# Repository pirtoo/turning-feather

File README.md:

# turning-feather
## Turning controller based on an Adafruit [Feather HUZZAH32](https://www.adafruit.com/product/3405) or [Feather ESP32 V2](https://www.adafruit.com/product/5400)

# This branch

This branch is testing LVGL and associated GUI libraries and a major restructuring of the code.
WiFi connectivity is working, it will create its own WiFI network if it cannot connect elsewhere.
LVGL display with dropdowns for program and stage selections, progress bars for the current exposure/away and for the stage as a whole are working.

Either disable WiFi or set a password on the WiFi network and an admin password on settings change.
There is a config menu on the device to reset settings if they are forgotten, to disable WiFi entirely and a signal strength meter for the ZPT RF remote control.

Still to come are popup messages for any errors or WiFi issues and if the ZPT remote control is low on battery or is not properly paired.

## Features

* More flexible than an [Auto Duel](https://web.archive.org/web/20170504011814/http://www.indelfa.co.uk/tt/ttcontruk.html) controller (and indelfa seem to have vanished), programs defined in JSON in a text file on a micro SD card. Can have a backup config file flashed to SPI accessed via LittleFS.

  * Current maximums of approx 55 programs and up to 12 stages per program (limited by memory in the controller) but will increase with development and it will be easier to swap between sets of programs.

  * [Example config](data/turnconf.txt).

  * Configs can be checked for JSON validity [here](https://arduinojson.org/v7/assistant/) or on any JSON website with a checker.

* Touch screen to select program/stage and start/stop face/away.

* RF remote control via [RF Solutions](https://www.rfsolutions.co.uk/) [ZPT module](https://www.rfsolutions.co.uk/radio-modules/zpt-433-868mhz-radio-telemetry-modules/?searchid=35864&search_query=zpt), compatable with their 4 button [Fobber](https://www.rfsolutions.co.uk/remote-control-systems/fobber-433mhz-868mhz-remote-control-key-fob-transmitter/?searchid=35862&search_query=fobber) or longer range [Trap](https://www.rfsolutions.co.uk/remote-control-systems/trap-handheld-transmitters-868mhz-or-918mhz-versions/?searchid=35863&search_query=trap) remote.

  Remote buttons give:
  * start/stop
  * face/away
  * stage -
  * stage +

  You can set a program and walk down range without needing to return to the unit to run, stop or change stages. The buzzer chirps briefly by default when changing stage from the RF remote so if you are unsure which stage you are in you can go to the first or last stage (when it cannot go further so will not chirp) to establish what stage is set.

  ZPT module can be programmed to respond to several different remotes. See the [ZPT datasheet](https://www.rfsolutions.co.uk/content/download-files/ZPT-3-DATASHEET.pdf) for programming instructions. I keep the learning button internal to the unit so it can't be accidentally activated.

* Display is a [Featherwing 2.4" TFT](https://www.adafruit.com/product/3315) or [Featherwing 2.4" TFT V2](https://www.adafruit.com/product/3315).

* Optional WiFi control, with no configuration and with WiFi enabled the controller will create a WiFi network called `TurningFeather`. Connecting to that network with no password and connecting to `http://192.168.4.1/` will get you to the control page. `http://192.168.4.1/wifisetup.html` will allow you to change setup of network names and joining an existing WiFi network. The MAC address for the controller is displayed on the setup page and also over serial console while booting for setting ststic
IP addresses on your router or IP can be set on the device (not recommended). Pages like `wifisetup.html` can be protected by an admin password (default username is `admin`) but this is all sent over unencrypted HTTP so is not high security, just to keep prying fingers out.

* Control/power connector is RJ45; takes ground, +12V power and two signal lines for face and away activation at 12V. As used [here](https://web.archive.org/web/20190102055407/http://www.indelfa.co.uk/tt/tt_images/relay.gif).  The control and power connections are exposed to another optional board connector if you do not want to use a PCB mounted RJ45.

* [Parts list and assembly details](PCBs/README.md).

## Current state

* Software build and flash [managed by PlatformIO](platformio.md) for different versions of ESP32 and display boards.

* [Custom PCB](PCBs/kicad/turning-feather) made for the main IO board manufactured by [PCBWay](https://www.pcbway.com/project/shareproject/Turning_Feather.html). See [schematic](PCBs/kicad/turning-feather/turning-feather.pdf).

* New generation of graphics are in progress.

* Two physical buttons for face/away and start/stop. Program selection via the touchscreen. Start/stop, face/away and stage +/- via RF remote.

* If `USE_ZPT_SERIAL` is enabled the controller detects when it receives a packet from a remote that is not paired with the comntroller and displays a `?` character in the top right hand corner of the display. Similarly if the battery in the transmitter is low then it will display a `!` character. These characters clear the next time the controller receives a packet from a paired receiver that does not have a low battery.

* With an ESP32 V2 there is a Neopixel LED on the board, if enabled by default this will light up white during initial setup and Red/Green/Blue for beep/face/away during stages. It points backwards but if using the case with a mostly clear front it should be visible to see what part of a stage the unit is in and if it has finished from further away. This can be enabled/disabled with the `ESP_V2_NEOPIXEL` macro and the overall brightness set with `ESP_V2_NEOPIXEL_BRIGHTNESS`

* Spare 5v output for light flash or other features.

## Future plans

Turning Feather is still very much in alpha and under development however it has been in use at one club for over 6 years.

- [ ] Config GUI to change system settings.

- [ ] Signal strength meter for the RFSolutions system.

- [ ] Add a stage name/comment to describe what each stage is for.

- [X] The [Feather HUZZAH32](https://www.adafruit.com/product/3405) microcontroller includes wifi, this will be used for setup, programming and control.

- [ ] Ability to change which config file is in use.

- [X] Updates planned here to provide [parts lists](PCBs/README.md), links, etc, to allow others to build their own units.

- [ ] Provide a full definition of the config file and what all the options do.

- [ ] Add random range options for configs for face/away times.

- [ ] Add the ability to use cheaper 433MHz radio transmitters (there are some nice 4/6 button units available) as an option but getting reliable detection of events with debouncing is hard to do well, unlike with the [RF Solutions](https://www.rfsolutions.co.uk/) units.

- [X] Support for the V2 versions of Adafruit Feather/Featherwing products used.

Other TODOs in the code are noted in the [main ino file](arduino/turning/turning.ino).

No plans to sell pre-made units in any volume but I may have one spare to sell that has not been installed in a case.

## Pull requests invited.

Feature request also invited.

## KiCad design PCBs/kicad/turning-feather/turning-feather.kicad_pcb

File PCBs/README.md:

# turning feather PCB and build

## Parts list to assemble with PCB

| Part | Quantity | Source |
| ---- | -------- | ------ |
| Capacitors |
| 0.1uF | x1 | |
| 22uF | x1 | |
| 470uF | x1 | |
| Resistors |
| 560R | x1 | |
| 2.2kR | x1 | |
| 10kR | x4 | |
| Diodes |
| 3mm LED | x2 | |
| 1N5817 | x4 | https://uk.farnell.com/stmicroelectronics/1n5817/diode-schottky-1a-20v-do-41/dp/9801197 |
| Connectors and cables |
| Socket headers | x1 pack | https://thepihut.com/products/36-pin-swiss-female-socket-headers-pack-of-5 |
| JST-PH 3 way PCB 90 degree | x1 | https://thepihut.com/products/jst-ph-jumper-assembly-3-wire |
| JST-PH 3 way plug and cable | x1 | Included in above |
| JST-PH 4 way PCB 90 degree | x1 | https://thepihut.com/products/jst-ph-jumper-assembly-4-wire |
| JST-PH 4 way plug and cable | x1 | Included in above |
| RJ45 PCB Shielded | x1 | https://uk.farnell.com/wurth-elektronik/615008142621/rj45-conn-r-a-jack-8p8c-1port/dp/2827822?gross_price=true&CMP=KNC-GUK-GEN-SHOPPING-PMAX-HIGH-ROAS&gad_source=1&gad_campaignid=17568744370&gclid=CjwKCAiA09jKBhB9EiwAgB8l-Keu6t1KMnuOvlgZ3LdBT3_u35CNMEyAGO-oGcBRlu94OLG5bAtN4hoCo3kQAvD_BwE |
| Panel Mount Extension USB Cable | x1 | [For Feather V1](https://thepihut.com/products/panel-mount-extension-usb-cable-micro-b-male-to-micro-b-female) [for V2](https://shop.pimoroni.com/products/right-angle-panel-mount-extension-cables-25cm?variant=32013609664595) |
| SMA to uFL cable | x1 | https://thepihut.com/products/sma-to-ufl-u-fl-ipx-ipex-rf-adapter-cable or included with antenna |
| SMA antenna | x1 | https://thepihut.com/products/lora-antenna-with-pigtail-868mhz-black |
| Adafruit Stacking Headers for Feather | x1 | https://thepihut.com/products/stacking-headers-for-feather-12-pin-and-16-pin-female-headers |
| Switches |
| Panel mount DPDT toggle switch | x1 | https://www.adafruit.com/product/3220?srsltid=AfmBOopktvlaYSxf00hTX3HSPP8zWhvR285GFbeFXXPOa2BU2tYauQCs |
| 6mm PCB button | x1 | https://thepihut.com/products/metal-ball-tactile-button-6mm-x-10-pack |
| Panel mount push buttons | x2 | https://thepihut.com/products/12mm-domed-push-button-6-pack |
| Boards and ICs | | |
| Feather ESP32 | x1 | [V1](https://thepihut.com/products/adafruit-huzzah32-esp32-feather-board-pre-soldered-ada3591) [V2](https://thepihut.com/products/adafruit-esp32-feather-v2-w-fl-antenna-8mb-flash-2-mb-psram-stemma-qt) |
| TFT FeatherWing - 2.4" 320x240 | x1 | [V2](https://thepihut.com/products/adafruit-tft-featherwing-2-4-320x240-touchscreen-for-all-feathers) |
| ZPT receiver DIP 868Mhz | x1 | https://www.rfsolutions.co.uk/radio-modules/zpt-433-868mhz-radio-telemetry-modules/?searchid=35864&search_query=zpt |
| TSR 1-2450 | x1 | https://uk.farnell.com/tracopower/tsr-1-2450/converter-dc-dc-5v-1a-sip/dp/1696320 |
| 4427 mosfet driver DIP-8 | x2 | https://uk.farnell.com/maxim-integrated-products/max4427epa/mosfet-driver-high-low-side-dip/dp/2516370 |
| Other |
| PCB | x1 | https://www.pcbway.com/project/shareproject/Turning_Feather.html |
| Remote control 868Mhz 4 buttons | x1 | https://www.rfsolutions.co.uk/remote-control-systems/fobber-433mhz-868mhz-remote-control-key-fob-transmitter/ or https://www.rfsolutions.co.uk/remote-control-systems/trap-handheld-transmitters-868mhz-or-918mhz-versions/ |
| 5v buzzer | x1 | https://thepihut.com/products/buzzer-5v-breadboard-friendly |
| M2.5 plastic standoff kit | x1 | https://thepihut.com/products/adafruit-black-nylon-screw-and-stand-off-set-m2-5-thread |
| Case Grey ABS Box Clear Lid 150x80x76 | x1 | https://thepihut.com/products/small-plastic-project-enclosure-weatherproof-with-clear-top |
| LiPo backup battery | x1 | https://thepihut.com/products/150mah-3-7v-lipo-battery |
| MicroSD card 1Gb-32Gb | x1 | |

One of the 1N5817 diodes should be inserted into the 5v supply line in the panel mount extension cable so when the unit has 12v supply, converting to 5V via the TSR 1-2450, this does not feed back to a USB connected device. 5v can be supplied either through the converter or from USB. If you do not install this diode I would not recommend connecting the controller to 12V and USB at the same time.

Input voltage is stated at 12v since this is what the original system uses. Minimum input voltage via the RJ45 is 6.5v and maxium input voltage is 36v to the TSR 1-2450. Maximum input voltage to the MAX4427EPA+ is 18v. Voltage output to the turn/away signals will be the input voltage.

The DPDT toggle switch turns the unit on and off and connects to J1 via the JST-PH 4 way cable. Pins 2 and 3 to each common on the switch, pin 1 to pin 2 in one position and pin 3 to pin 4 in the other position. In the off position 12v from the PCB RJ45 is not supplied back to the board and the enable pin of the Feather is grounded.

The two panel switches and the buzzer connect to J3 via the JST-PH 3 way cable. Pin 1 to the buzzer positive pin, pin 3 to the buzzer ground. Pin 2 to the first button and to a resistor to the second button and ground to the other button pins. This way when the button is pressed pin 2 is grounded directly, when the other button is pressed pin 2 is grounded via the resistor.

With the HUZZAH32/ESP32 you cannot read analog inputs on ADC #2 once WiFi has started as it is shared with the WiFi module. This pin is used as a digital input from the radio receiver so this should not cause problems. Maximum current output from each output pin is 1.1 mA, hence running the buzzer through a mosfet driver.

## Options

The LiPo battery to connect to the Feather is optional, a small battery is useful for using the controller when not connected to the target system and in case power is temporarily interrupted. A small battery will fit under the Feather board and connect to it.

Instead of using a PCB mounted RJ45 connector the optional J2 connector can be used to connect to 12v supply, ground, and turn/away signals. If you are not using J2 there is no need to fit a connector.

If you do not need a buzzer then U3 can be left off. The output will still flash the onboard LED by default. J3 pin 2 can be left unconnected.

# Assembly

Be careful to orient diodes, LEDs and tantalum/electrolytic capacitors correctly.

Note that some components (RJ45, LEDs and learn button) are placed on the rear side of the PCB.

The ZPT antenna is connected via the uFL connector on the ZPT board.

Plastic M2.5 standoffs should be used to mount the Featherwing display and HUZZAH32 to the IO board. Note that two of the mounting holes on the HUZZAH32 are partially obscured by the onboard 2.4GHz antenna so cannot be used.

V2 of the Adafruit ESP32 Feather is now supported as are V2 Adafruit display Featherwings, make sure to build the correct version for the hardware revisions you have. An ESP32 is required for the current code since it uses ESP32 timers.

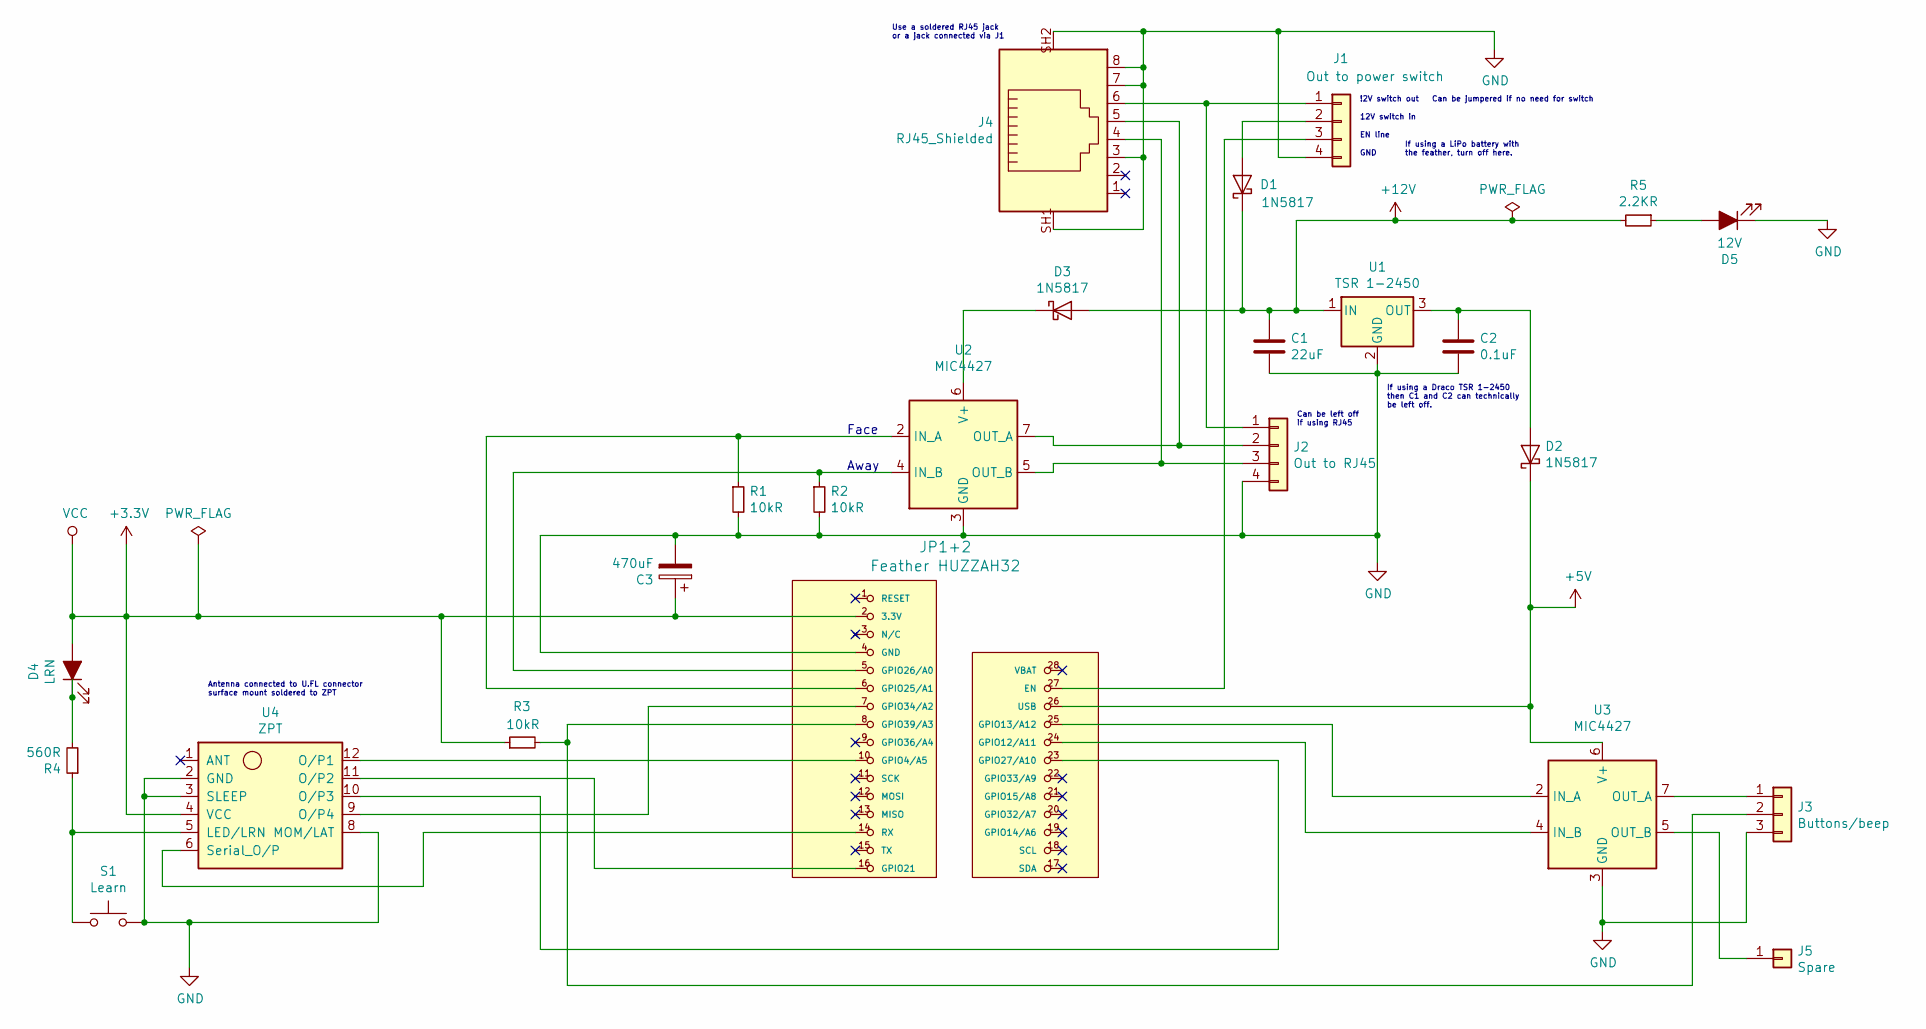
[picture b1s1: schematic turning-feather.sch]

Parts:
C1: 22uF; CP_Radial_Tantal_D4.5mm_P2.50mm
C2: 0.1uF; C_Disc_D3.0mm_W2.0mm_P2.50mm
C3: 470uF; CP_Radial_D6.3mm_P2.50mm
D1, D2, D3: 1N5817; D_DO-41_SOD81_P10.16mm_Horizontal
D4: LRN; LED_D3.0mm_Clear
D5: 12V; LED_D3.0mm_Clear
J1: Out to power switch; JST_PH_S4B-PH-K_1x04_P2.00mm_Horizontal
J2: Out to RJ45; JST_PH_S4B-PH-K_1x04_P2.00mm_Horizontal
J3: Buttons/beep; JST_PH_S3B-PH-K_1x03_P2.00mm_Horizontal
J4: RJ45_Shielded; RJ45_Horizontal_Shielded
J5: Spare; PinHeader_1x01_P1.00mm_Vertical
JP1+2: Feather HUZZAH32; ADAFRUIT_FEATHER
R1, R2, R3: 10kR; R_Axial_DIN0207_L6.3mm_D2.5mm_P7.62mm_Horizontal
R4: 560R; R_Axial_DIN0207_L6.3mm_D2.5mm_P7.62mm_Horizontal
R5: 2.2KR; R_Axial_DIN0207_L6.3mm_D2.5mm_P7.62mm_Horizontal
S1: Learn; SW_PUSH_6mm_H5mm
U1: TSR 1-2450; Converter_DCDC_TRACO_TSR-1_THT
U2, U3: MIC4427; DIP-8_W7.62mm
U4: ZPT; ZPT8RD

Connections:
+3V3: C3.1, D4.2 (A), JP1+2.2 (3.3V), R3.1, U4.4 (VCC)
+5V: D2.1 (K), JP1+2.26 (USB), U3.6 (V+)
+12V: C1.1, D1.1 (K), D3.2 (A), R5.2, U1.1 (IN)
GND: C1.2, C2.2, C3.2, D5.1 (K), J1.4, J2.4, J3.3, J4.3, J4.7, J4.8, J4.SH1, J4.SH2, JP1+2.4 (GND), R1.2, R2.2, S1.2, U1.2 (GND), U2.3 (GND), U3.3 (GND), U4.2 (GND), U4.3 (SLEEP), U4.8 (MOM/LAT)
unnamed: C2.1, D2.2 (A), U1.3 (OUT)
unnamed: D1.2 (A), J1.2
unnamed: D3.1 (K), U2.6 (V+)
unnamed: D4.1 (K), R4.2
unnamed: D5.2 (A), R5.1
unnamed: J1.1, J2.1, J4.6
unnamed: J1.3, JP1+2.27 (EN)
unnamed: J2.2, J4.5, U2.7 (OUT_A)
unnamed: J2.3, J4.4, U2.5 (OUT_B)
unnamed: J3.1, U3.7 (OUT_A)
unnamed: J3.2, JP1+2.8 (GPIO39/A3), R3.2
unnamed: J5.1, U3.5 (OUT_B)
unnamed: JP1+2.5 (GPIO26/A0), R2.1, U2.4 (IN_B)
unnamed: JP1+2.6 (GPIO25/A1), R1.1, U2.2 (IN_A)
unnamed: JP1+2.7 (GPIO34/A2), U4.9 (O/P4)
unnamed: JP1+2.10 (GPIO4/A5), U4.12 (O/P1)
unnamed: JP1+2.14 (RX), U4.6 (Serial_O/P)
unnamed: JP1+2.16 (GPIO21), U4.11 (O/P2)
unnamed: JP1+2.23 (GPIO27/A10), U4.10 (O/P3)
unnamed: JP1+2.24 (GPIO12/A11), U3.4 (IN_B)
unnamed: JP1+2.25 (GPIO13/A12), U3.2 (IN_A)
unnamed: R4.1, S1.1, U4.5 (LED/LRN)

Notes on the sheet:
Face
Away
If using a Draco TSR 1-2450 then C1 and C2 can technically be left off.
If using a LiPo battery with the feather, turn off here.
Antenna connected to U.FL connector surface mount soldered to ZPT
Use a soldered RJ45 jack or a jack connected via J1
Can be jumpered if no need for switch
Can be left off if using RJ45
!2V switch out
12V switch in
EN line
GND

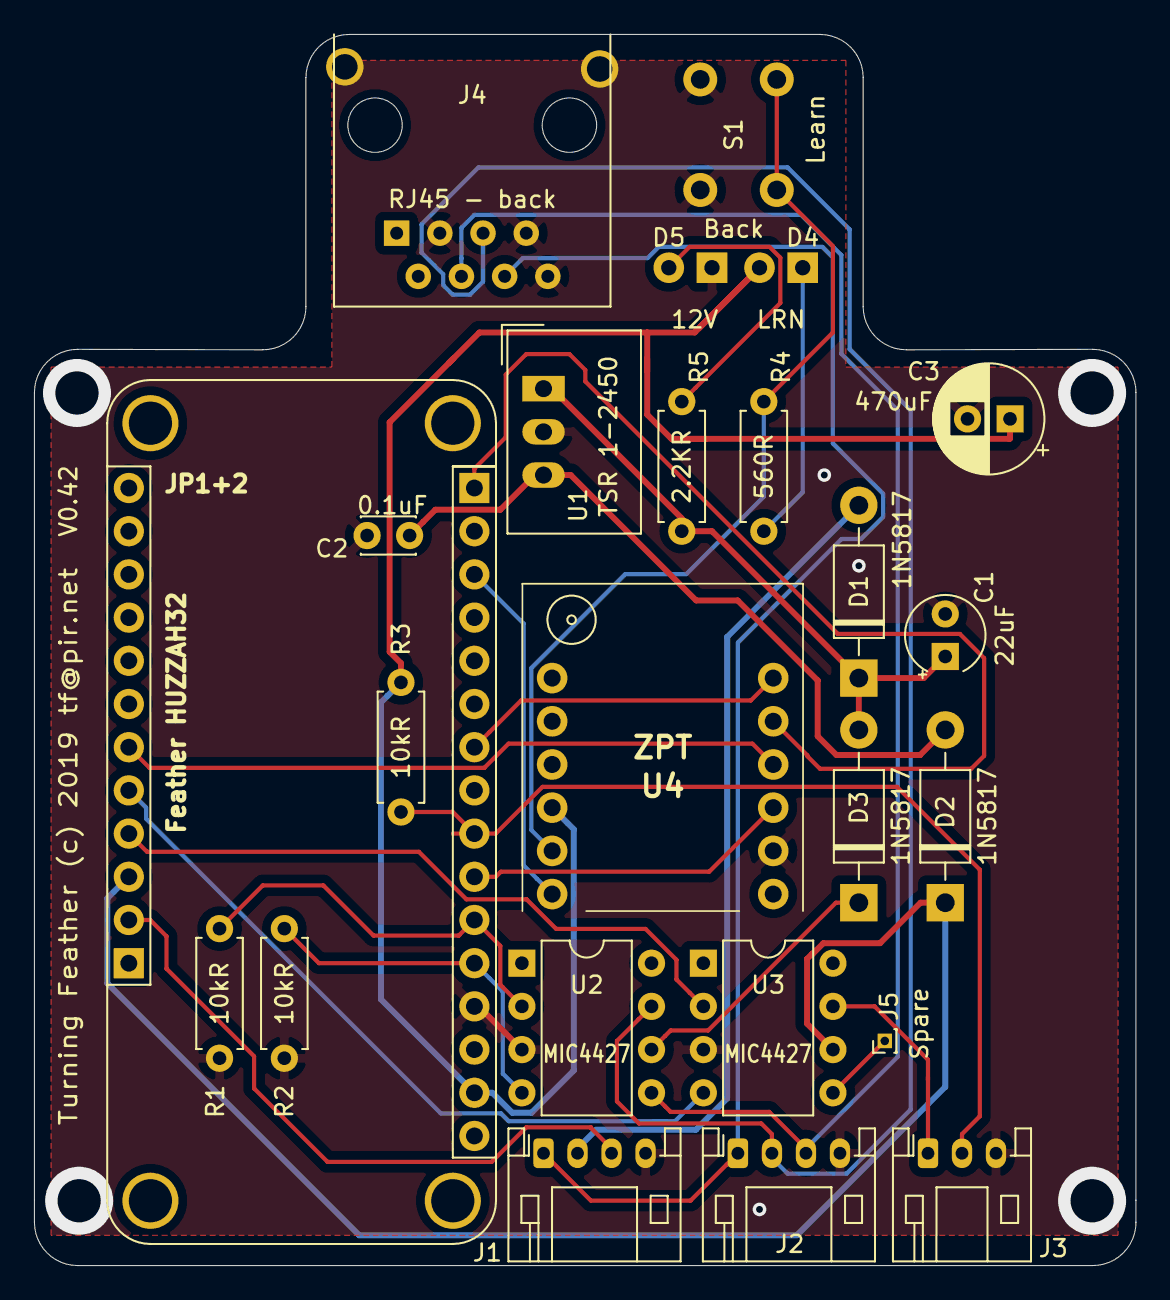
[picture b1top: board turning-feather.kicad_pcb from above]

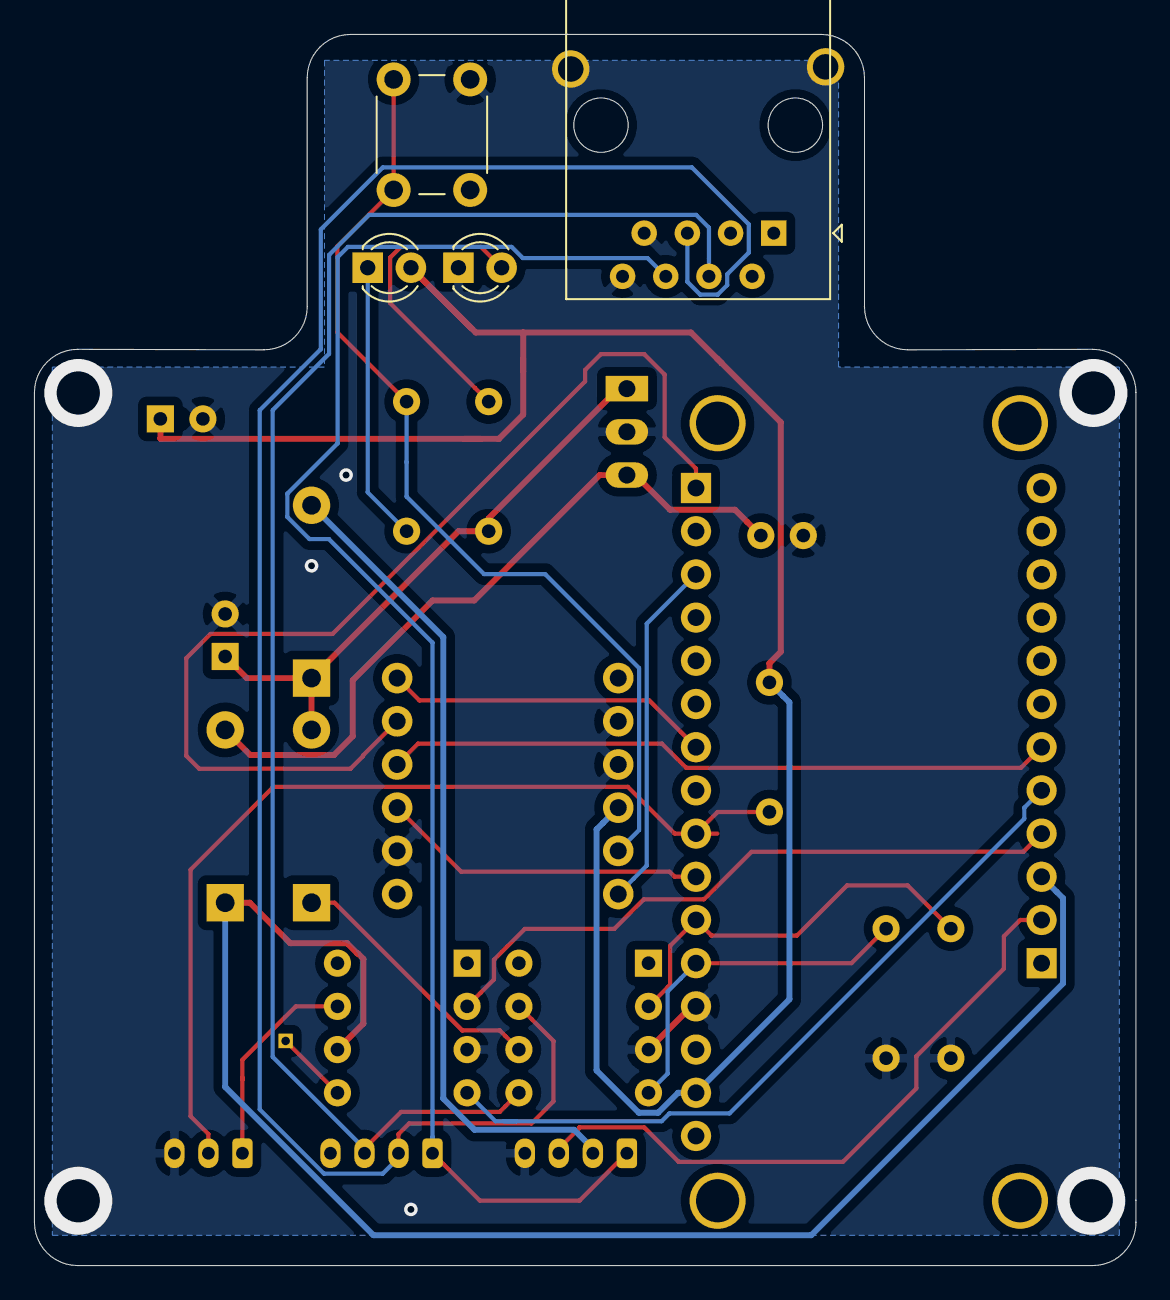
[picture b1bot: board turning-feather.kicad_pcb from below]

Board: 2 copper layers, 64.8 x 72.4 mm, 24 parts (4 on the bottom side), 26 nets.

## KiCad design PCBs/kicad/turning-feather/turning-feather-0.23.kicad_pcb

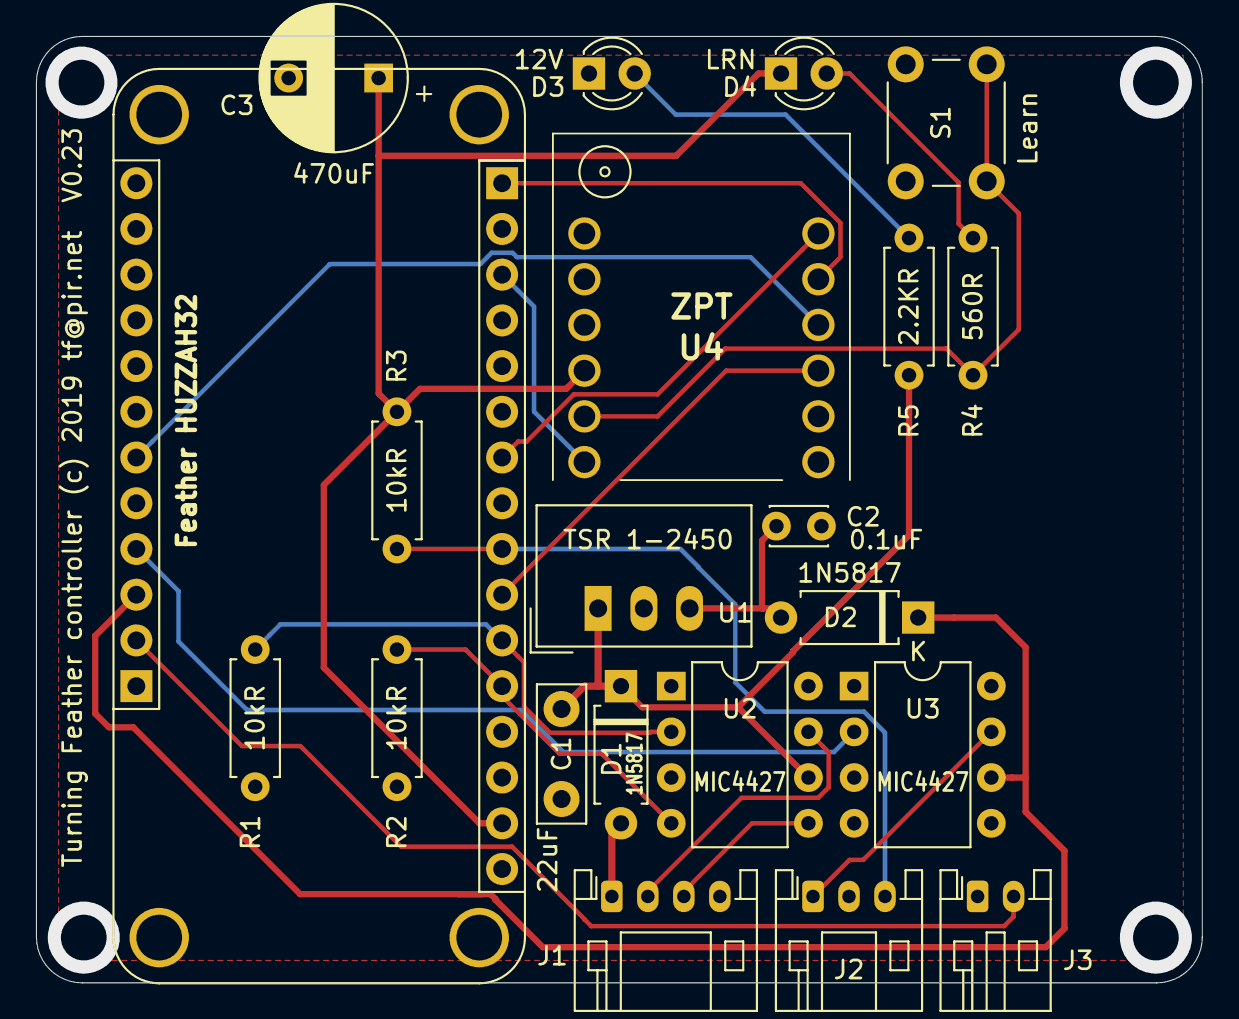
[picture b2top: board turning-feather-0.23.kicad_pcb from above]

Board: 2 copper layers, 64.8 x 52.6 mm, 21 parts (0 on the bottom side), 22 nets.

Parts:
C1: 22uF; C_Disc_D7.5mm_W2.5mm_P5.00mm
C2: 0.1uF; C_Disc_D3.0mm_W2.0mm_P2.50mm
C3: 470uF; CP_Radial_D8.0mm_P5.00mm
D1, D2: 1N5817; D_A-405_P7.62mm_Horizontal
D3: 12V; LED_D3.0mm_Clear
D4: LRN; LED_D3.0mm_Clear
J1: Out to RJ45; JST_PH_S4B-PH-K_1x04_P2.00mm_Horizontal
J2: Buttons/beep; JST_PH_S3B-PH-K_1x03_P2.00mm_Horizontal
J3: Off switch; JST_PH_S2B-PH-K_1x02_P2.00mm_Horizontal
JP1: Feather HUZZAH32; ADAFRUIT_FEATHER
R1, R2, R3: 10kR; R_Axial_DIN0207_L6.3mm_D2.5mm_P7.62mm_Horizontal
R4: 560R; R_Axial_DIN0207_L6.3mm_D2.5mm_P7.62mm_Horizontal
R5: 2.2KR; R_Axial_DIN0207_L6.3mm_D2.5mm_P7.62mm_Horizontal
S1: Learn; SW_PUSH_6mm_H5mm
U1: TSR 1-2450; Converter_DCDC_TRACO_TSR-1_THT
U2, U3: MIC4427; DIP-8_W7.62mm
U4: ZPT; ZPT8RD

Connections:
+3V3: C3.1, D4.1, JP1.2, R3.1, U4.4
+5V: D2.1, JP1.26, U3.6
+12V: C1.1, D1.1, R5.1, U1.1, U2.6
GND: C1.2, C2.2, C3.2, D3.1, J1.4, J2.2, J3.1, JP1.4, R1.2, R2.2, S1.2, U1.2, U2.3, U3.3, U4.2, U4.3, U4.8
unnamed: C2.1, D2.2, U1.3
unnamed: D1.2, J1.1
unnamed: D3.2, R5.2
unnamed: D4.2, R4.2
unnamed: J1.2, U2.7
unnamed: J1.3, U2.5
unnamed: J2.1, U3.7
unnamed: J2.3, JP1.8, R3.2
unnamed: J3.2, JP1.27
unnamed: JP1.5, R2.1, U2.4
unnamed: JP1.6, R1.1, U2.2
unnamed: JP1.7, U4.9
unnamed: JP1.10, U4.12
unnamed: JP1.14, U4.6
unnamed: JP1.16, U4.11
unnamed: JP1.23, U4.10
unnamed: JP1.25, U3.2
unnamed: R4.1, S1.1, U4.5

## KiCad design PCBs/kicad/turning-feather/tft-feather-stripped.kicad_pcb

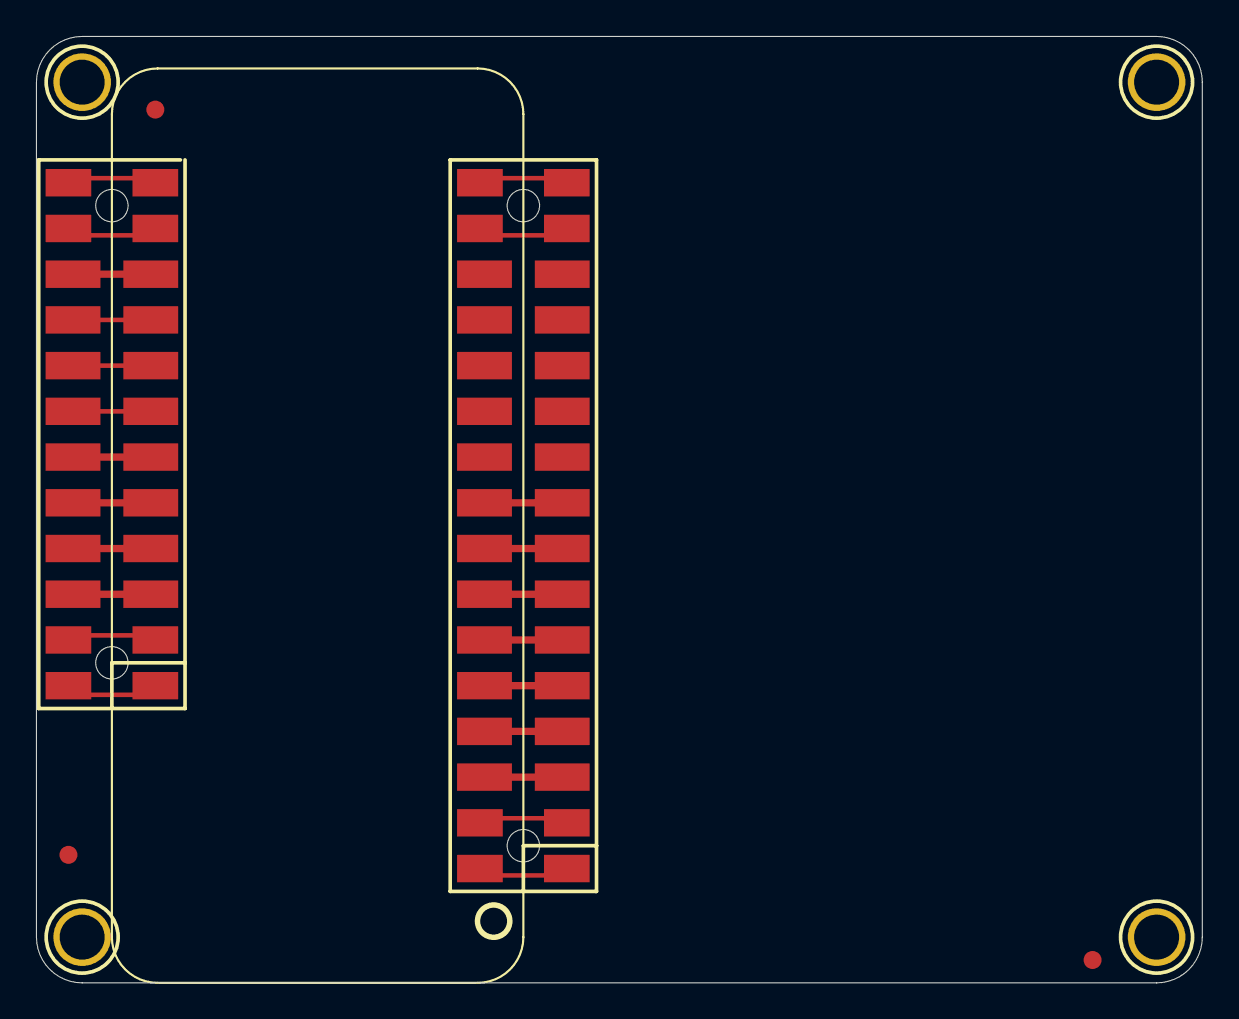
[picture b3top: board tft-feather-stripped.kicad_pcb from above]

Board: 16 copper layers, 64.8 x 52.6 mm, 9 parts (0 on the bottom side), 28 nets.

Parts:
FID1, FID2, FID3: FIDUCIAL; FIDUCIAL_1MM
MS2: FEATHERWING_SMTDUAL; FEATHERWING_SMT2
U$9, U$11, U$15, U$17: MOUNTINGHOLE2.5; MOUNTINGHOLE_2.5_PLATED
U$34: PCBFEAT-REV-040

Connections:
3.3V: MS2.2, MS2.2'
/MISO: MS2.13, MS2.13'
/MOSI: MS2.12, MS2.12'
/SCLK: MS2.11, MS2.11'
GND: MS2.4, MS2.4'
unnamed: MS2.1, MS2.1'
unnamed: MS2.3, MS2.3'
unnamed: MS2.5, MS2.5'
unnamed: MS2.6, MS2.6'
unnamed: MS2.7, MS2.7'
unnamed: MS2.8, MS2.8'
unnamed: MS2.9, MS2.9'
unnamed: MS2.10, MS2.10'
unnamed: MS2.14, MS2.14'
unnamed: MS2.15, MS2.15'
unnamed: MS2.16, MS2.16'
unnamed: MS2.17, MS2.17'
unnamed: MS2.18, MS2.18'
unnamed: MS2.19, MS2.19'
unnamed: MS2.20, MS2.20'
unnamed: MS2.21, MS2.21'
unnamed: MS2.22, MS2.22'
unnamed: MS2.23, MS2.23'
unnamed: MS2.24, MS2.24'
unnamed: MS2.25, MS2.25'
unnamed: MS2.26, MS2.26'
unnamed: MS2.27, MS2.27'
unnamed: MS2.28, MS2.28'

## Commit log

2019-08-28 Initial set of arduino files and kicad files for turning feather
2019-08-28 Add to readme a little
2019-08-29 Set to max programs tested and clean up some error output
2019-08-29 Reformat a print and add a TODO
2019-08-29 Add serial output from ZPT to serial in on feather. PCB V0.23.
2019-08-29 Update schematic with plotted pdf
2019-08-31 Add parsing of ZPT serial data and unify block comment styles
    The ZPT unit outputs a serial data packet format with information
    about received signal from a transmitter. If this is connected to Serial2
    on the feather HUZZAH32 we can parse it and get informaiton such as
    transmitter low battery or if the button has been learned by the
    receiver and print up a status character int the top right to warn the user
    '!' means low battery and '?' means unlearned button code.
2019-08-31 PCB version 0.32.
    Add serial connection from ZPT to Serial2 on HUZZAH32.
    Connect spare 5V MOSFET input to spare HUZZAH32 output with header.
    Add on-board PCB mount RJ45 as an option, old connector retained.
    Move LEDs out to new board extension back to point towards user.
2019-08-31 Refactor SD section out
2019-09-06 Split out sd/spiffs handling a little, add TFT_eSPI and bmp display
2019-09-06 Move ethernet on-PCB, move most things around, change capacitors, etc
2019-09-07 Clean up filled areas a little
2019-09-07 Some cleanup to pcb and schema
2019-09-08 Small cleanups for v0.41
2019-09-08 Fixups for better language use and use better fonts with newer library
2019-09-10 Fix dimension markers to the new lower edge of the board
2019-09-10 Add HUZZAH32/featherwing tft 2.4" guislice setup file
2019-09-16 Move DIL base slightly over to provide room for header sockets to be used
2019-09-16 Update external schematic with options
2019-09-16 Add schematic pdfs for current rev
2019-09-17 Fix some minor labelling issues
2019-09-17 Label diode and add text to external schema
2019-09-18 When stopping make sure the beep stops then rather than later
2019-09-18 Add floating point
2019-09-18 Add some fudge horizontally for pressing screen buttons
2019-09-24 Slight tweaks for fitting
2019-10-25 Fix the number of repeats for a granet
2019-11-09 Make sure zpt serial setup is done before looping
2019-11-09 Store if SD or SPIFFS init was ok for later use
2019-11-09 Update turning configuration read/write
    Default and minimum repeats is 1, enforcing display behaviour because
    it looks odd otherwise.
    Rename capacity variables to turn_capacity to allow for other configs
    (like system).
    Expand comments.
2019-11-09 tweak guislice config for later use
2019-11-09 Add ESP32 specific restart utility
2019-11-09 turning.ino updates for logic, etc
    Fix logic in not quite a state machine so states are not skipped
    through (wasting a tick and causing a flicker on the screen) if they
    are not going to be used (because the option is zero).
    Fix logic if autonext is set on the last stage in a program.
    ifdef out more ZPT serial sections if zpt serial is not used.
    Make sure timer stops when running stops.
2019-11-09 Add BAR's Warfield Standard program
2019-11-09 Make sure last stage does not have autonext or nextaway set
2019-11-09 make WS formatting clearer
2019-11-09 Revert turn_lcd changes that are not ready
2019-11-09 Update readme and images
2019-11-09 Clean up old versions and give an ignored directory to stash them
2019-11-09 Add board version 0.42 gerber plots
2019-11-09 remove double comment
2019-11-09 Allow RX2 definitions to be overridden and mode them into the .h
2021-04-20 Add more MRPC courses of fire
2021-04-20 Make beep times consistent
2021-05-01 Alter sixpack to all 10s without flash
2021-06-11 Remove the option for arduino gfx library because later options will require TFT_eSPI
2021-06-11 Simpligy change timer and give the option of keeping output lines high during a stage
2021-06-11 Cleanup unused function, etc
2021-06-11 Config gui test
2021-06-12 Move indelfa links to wayback machine since the original site is gone
2021-06-14 Link to replaecment 4 button Trap remote
2021-08-23 Fix link to display board
2022-04-12 Add Multi Target Countdown
2025-12-30 Bring up to working with current versions of libraries and add a little more docs
2025-12-30 Typos
2026-01-01 Add PCB/construction documentation
2026-01-01 Update AnalogMultiButton values
2026-01-01 Update docs
2026-01-01 guislice config file is only used in gui testing branch
2026-01-01 Bring gui test up to current versions
2026-01-01 Add gui test comment
2026-01-02 Allow for Adafruit ESP32 V2 and streamline zpt serial use
2026-01-02 syntax
2026-01-02 Correct docs about 12v via J2
2026-01-04 Move arduino to platformio locations
2026-01-04 Major rework to use platformio, support new boards and drop TFT_eSPI since adafruit default libraries now do nice fonts
2026-01-04 Add image of unpaired remote display
2026-01-04 Add indelfa images
2026-01-04 README updates
2026-01-04 Remove incorrectly moved file
2026-01-04 Old turn_lcd
2026-01-04 New turn_lcd
2026-01-04 Add Neopixel support for ESP32 V2 boards
2026-01-04 Avoid no test directory errors
2026-01-04 Add docs for neopixel and define for brightness
2026-01-04 Docs comment on zpt serial
2026-01-06 Don't endless loop without a delay
2026-01-06 First stage of WiFi support; creates a network or joins a network and can manage wifi settings over wifi.
2026-01-06 Rework to split a lot of things out of turning.cpp. Put setup() and loop() and other basics into main.cpp. Move neopixel to own files.
2026-01-06 Refactor getting strings from Prefs
2026-01-06 Rename TF to TURN
2026-01-06 Remove utils, migrate remaining into main.h
2026-01-06 Cleanup
2026-01-06 More refactorying, rf buttons to own file
2026-01-06 Rename option to make more sense for other change source types
2026-01-06 Proof of concept getting the program list to a select in html
2026-01-07 Comments/moves
2026-01-08 Move wifi hostname set to before any use or it does not get used
2026-01-08 Get rid of a useless function
2026-01-12 Fix error codes
2026-01-12 Don't stop wifi
2026-01-12 Variable that isn't used and move function
2026-01-14 Usable wifi control page for controller
2026-01-14 index small simplifications
2026-01-14 Get rid of SPIFFS support
2026-01-14 Fixes and cleanup
2026-01-14 Update README with wifi
2026-01-14 Fix edge case where a large number of failed connections return at once and button text did not update
2026-01-14 Add wifi authentication and the options to manage it. Update docs, etc.
2026-01-14 Doc updates
2026-01-15 Fix typo
2026-01-15 Doc update
2026-01-17 Fix MAC disoplay for local AP as well as remote wifi connection
2026-01-19 Update flags
2026-01-19 Add partition schemes for 4 and 8mb boards
2026-01-21 Major restructure, addition of LVGL and EEZ libraries. Not finished yet, stage info is not displayed on screen.
2026-01-21 New splash image
2026-01-21 Docs update
2026-01-21 Save EEZ config before more tests
2026-01-24 Main functionality finished with LVGL, needs some extras still.

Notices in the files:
PCBs/kicad/turning-feather/turning-feather-0.23.kicad_pcb:
Turning Feather controller (c) 2019 tf@pir.net
PCBs/kicad/turning-feather/turning-feather.kicad_pcb:
Turning Feather (c) 2019 tf@pir.net
